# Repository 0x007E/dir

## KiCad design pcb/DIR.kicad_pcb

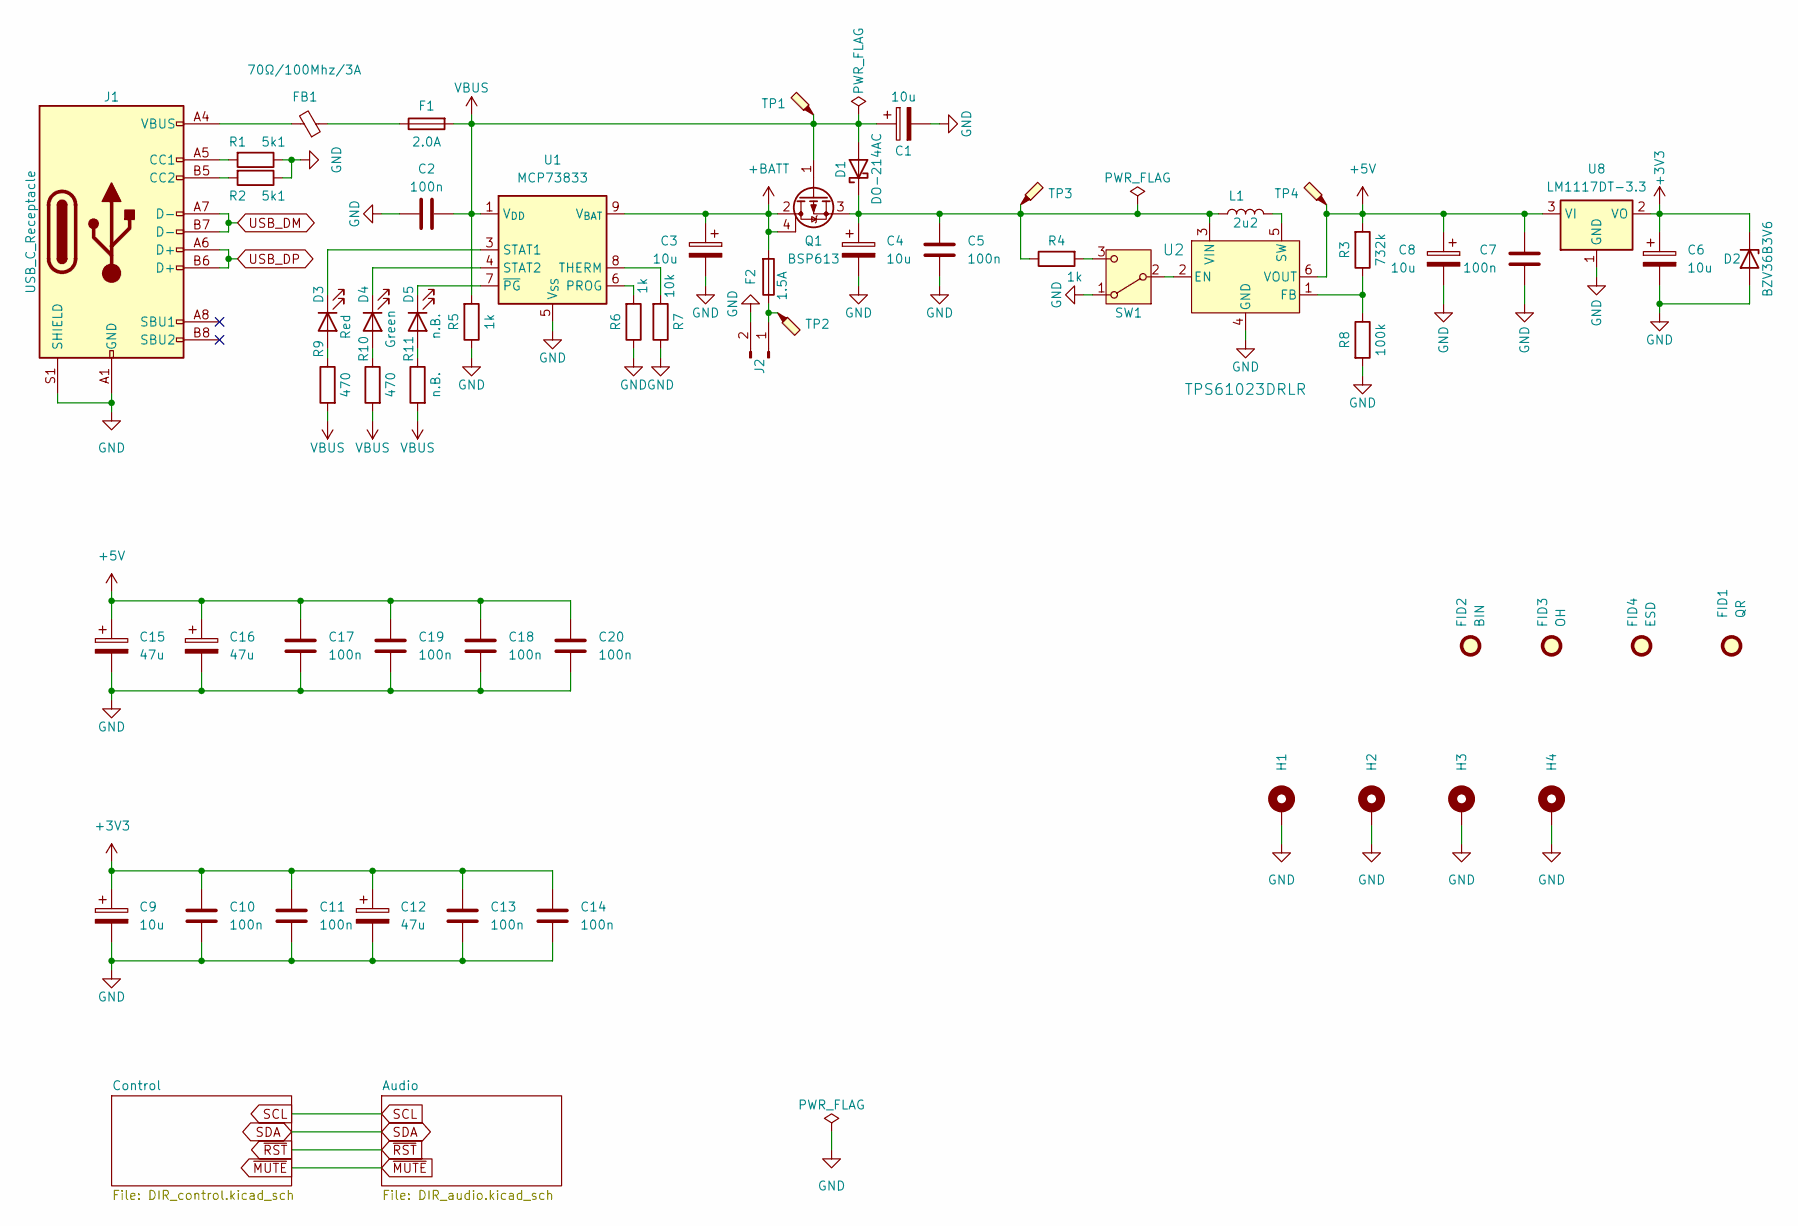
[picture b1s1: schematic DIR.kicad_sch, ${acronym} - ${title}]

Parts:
C1, C3, C4, C6, C8, C9: 10u; CP_EIA-6032-28_Kemet-C
C2, C5, C7, C10, C11, C13, C14, C17, C18, C19, C20: 100n; C_1206_3216Metric
C12, C15, C16: 47u; CP_EIA-6032-28_Kemet-C
D1: DO-214AC; D_SMA
D2: BZV36B3V6; D_MiniMELF
D3: Red; LED_1206_3216Metric
D4: Green; LED_1206_3216Metric
D5: n.B.; LED_1206_3216Metric
F1: 2.0A; Fuse_1206_3216Metric
F2: 1.5A; Fuse_1206_3216Metric
FB1: 70Ω/100Mhz/3A; L_1206_3216Metric
FID1: QR; QR_0x007e_very_small
FID2: BIN; WEEE-Logo_4.2x6mm_SilkScreen
FID3: OH; OSHW-Logo2_7.3x6mm_SilkScreen
FID4: ESD; ESD-Logo_6.6x6mm_SilkScreen
H1, H2: MountingHole_Pad; MountingHole_3.2mm_M3_DIN965_Pad
H3, H4: MountingHole_Pad; MountingHole_2.2mm_M2_Pad
J1: USB_C_Receptacle; USB_C_Receptacle_GCT_USB4110
J2: Conn_01x02_Pin; JST_PH_S2B-PH-K_1x02_P2.00mm_Horizontal
L1: 2u2; L_Vishay_IFSC-1515AH_4x4x1.8mm
Q1: BSP613; SOT-223
R1, R2: 5k1; R_1206_3216Metric
R3: 732k; R_1206_3216Metric
R4, R5, R6: 1k; R_1206_3216Metric
R7: 10k; R_1206_3216Metric
R8: 100k; R_1206_3216Metric
R9, R10: 470; R_1206_3216Metric
R11: n.B.; R_1206_3216Metric
SW1: SW_SPDT; SW_SPDT_CK_JS102011SAQN
TP1, TP2, TP3, TP4: TestPoint_Probe; TestPoint_Pad_D1.0mm
U1: MCP73833; MSOP-10_3x3mm_P0.5mm
U2: TPS61023DRLR; SOT-563
U8: LM1117DT-3.3; TO-252-3_TabPin2

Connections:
+3V3: C6.1, C9.1, C10.1, C11.1, C12.1, C13.1, C14.1, D2.1 (K), U8.2 (VO); also elsewhere on the board
+5V: C7.1, C8.1, C15.1, C16.1, C17.1, C18.1, C19.1, C20.1, R3.2, TP4.1, U2.6 (VOUT), U8.3 (VI); also elsewhere on the board
+BATT: C3.1, F2.2, Q1.2 (D), Q1.4 (D), U1.9 (V_{BAT}), U1.10 (V_{BAT})
GND: C1.2, C2.2, C3.2, C4.2, C5.2, C6.2, C7.2, C8.2, C9.2, C10.2, C11.2, C12.2, C13.2, C14.2, C15.2, C16.2, C17.2, C18.2, C19.2, C20.2, D2.2 (A), H1.1, H2.1, H3.1, H4.1, J1.A1 (GND), J1.A12 (GND), J1.B1 (GND), J1.B12 (GND), J1.S1 (SHIELD), J2.2, R1.1, R2.1, R5.1, R6.1, R7.1, R8.2, SW1.1 (A), U1.5 (V_{SS}), U2.4 (GND), U8.1 (GND); also elsewhere on the board
unnamed: C4.1, C5.1, D1.1 (K), L1.1, Q1.3 (S), R4.1, TP3.1, U2.3 (VIN)
unnamed: D3.2 (A), R9.1
unnamed: D3.1 (K), U1.3 (STAT1)
unnamed: D4.2 (A), R10.1
unnamed: D4.1 (K), U1.4 (STAT2)
unnamed: D5.2 (A), R11.1
unnamed: D5.1 (K), U1.7 (~PG)
unnamed: F1.1, FB1.1
unnamed: FB1.2, J1.A4 (VBUS), J1.A9 (VBUS), J1.B4 (VBUS), J1.B9 (VBUS)
unnamed: J1.A5 (CC1), R1.2
unnamed: J1.B5 (CC2), R2.2
unnamed: F2.1, J2.1, TP2.1
unnamed: SW1.2 (B), U2.2 (EN)
unnamed: R4.2, SW1.3 (C)
unnamed: R6.2, U1.6 (PROG)
unnamed: R7.2, U1.8 (THERM)
unnamed: R3.1, R8.1, U2.1 (FB)
unnamed: L1.2, U2.5 (SW)
USB_DM: J1.A7 (D-), J1.B7 (D-); also elsewhere on the board
USB_DP: J1.A6 (D+), J1.B6 (D+); also elsewhere on the board
VBUS: C1.1, C2.1, D1.2 (A), F1.2, Q1.1 (G), R5.2, R9.2, R10.2, R11.2, TP1.1, U1.1 (V_{DD}), U1.2 (V_{DD}); also elsewhere on the board

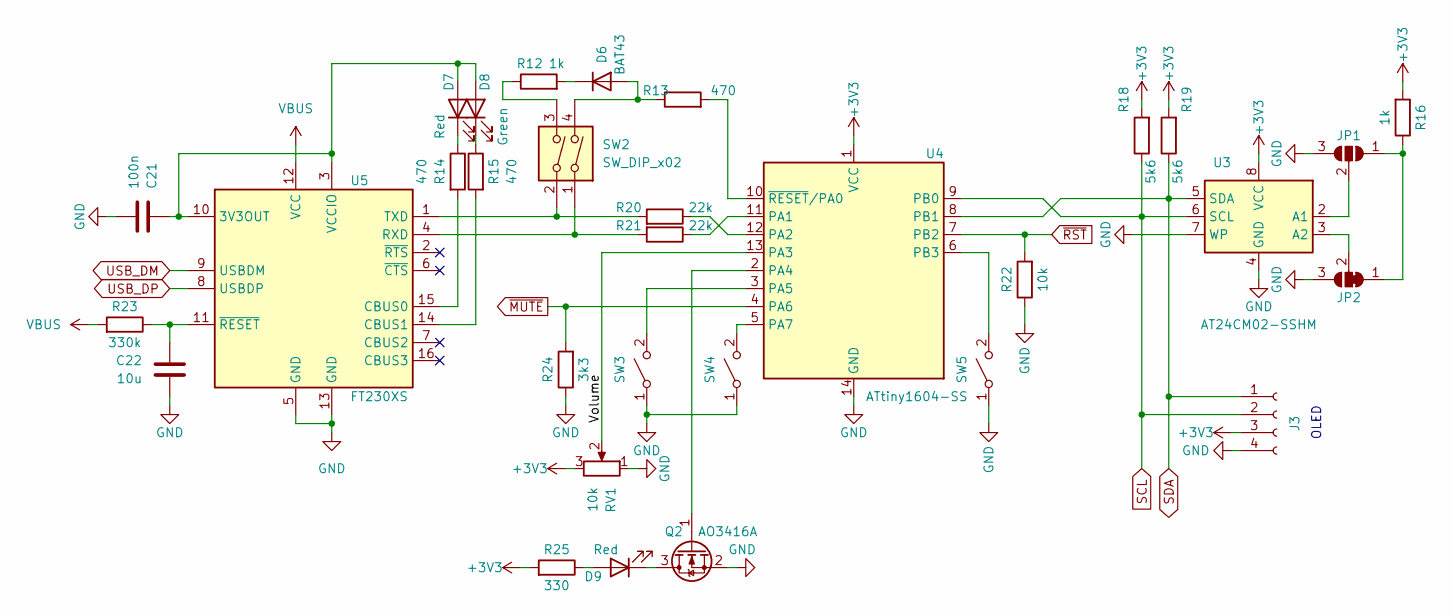
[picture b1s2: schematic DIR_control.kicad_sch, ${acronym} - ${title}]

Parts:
C21: 100n; C_1206_3216Metric
C22: 10u; C_1206_3216Metric
D6: BAT43; D_MiniMELF
D7, D9: Red; LED_1206_3216Metric
D8: Green; LED_1206_3216Metric
J3: Conn_01x04_Socket; PinSocket_1x04_P2.54mm_Vertical
JP1: SolderJumper_3_Open; SolderJumper-3_P1.3mm_Open_RoundedPad1.0x1.5mm_NumberLabels
JP2: SolderJumper_3_Bridged12; SolderJumper-3_P1.3mm_Bridged12_RoundedPad1.0x1.5mm_NumberL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
Q2: AO3416A; SOT-23
R12, R16: 1k; R_1206_3216Metric
R13, R14, R15: 470; R_1206_3216Metric
R18, R19: 5k6; R_1206_3216Metric
R20, R21: 22k; R_1206_3216Metric
R22: 10k; R_1206_3216Metric
R23: 330k; R_1206_3216Metric
R24: 3k3; R_1206_3216Metric
R25: 330; R_1206_3216Metric
RV1: 10k; Potentiometer_Piher_PT-10-V10_Vertical
SW2: SW_DIP_x02; SW_DIP_SPSTx02_Slide_6.7x6.64mm_W8.61mm_P2.54mm_LowProfile
SW3, SW4, SW5: SW_SPST; SW_Tactile_SPST_Angled_PTS645Vx58-2LFS
U3: AT24CM02-SSHM; SOIC-8_3.9x4.9mm_P1.27mm
U4: ATtiny1604-SS; SOIC-14_3.9x8.7mm_P1.27mm
U5: FT230XS; SSOP-16_3.9x4.9mm_P0.635mm

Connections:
+3V3: J3.3, R16.2, R18.2, R19.2, R25.2, RV1.3, U3.8 (VCC), U4.1 (VCC); also elsewhere on the board
/Control/Volume: RV1.2, U4.13 (PA3)
GND: C21.1, C22.2, J3.4, JP1.3 (B), JP2.3 (B), Q2.2 (S), R22.1, R24.1, RV1.1, SW3.1 (A), SW4.1 (A), SW5.1 (A), U3.4 (GND), U3.7 (WP), U4.14 (GND), U5.5 (GND), U5.13 (GND); also elsewhere on the board
unnamed: D6.2 (A), R13.1, SW2.4
unnamed: D6.1 (K), R12.2
unnamed: C21.2, D7.2 (A), D8.2 (A), U5.3 (VCCIO), U5.10 (3V3OUT)
unnamed: D7.1 (K), R14.1
unnamed: D8.1 (K), R15.1
unnamed: D9.2 (A), R25.1
unnamed: D9.1 (K), Q2.3 (D)
unnamed: JP1.1 (A), JP2.1 (A), R16.1
unnamed: JP1.2 (C), U3.2 (A1)
unnamed: JP2.2 (C), U3.3 (A2)
unnamed: Q2.1 (G), U4.2 (PA4)
unnamed: R12.1, SW2.3
unnamed: SW3.2 (B), U4.3 (PA5)
unnamed: SW4.2 (B), U4.5 (PA7)
unnamed: SW5.2 (B), U4.6 (PB3)
unnamed: R21.1, U4.11 (PA1)
unnamed: R20.1, U4.12 (PA2)
unnamed: R13.2, U4.10 (~RESET/PA0)
unnamed: R14.2, U5.15 (CBUS0)
unnamed: R15.2, U5.14 (CBUS1)
unnamed: R21.2, SW2.1, U5.4 (RXD)
unnamed: R20.2, SW2.2, U5.1 (TXD)
unnamed: C22.1, R23.1, U5.11 (~RESET)
SCL: J3.2, R18.1, U3.6 (SCL), U4.9 (PB0); also elsewhere on the board
SDA: J3.1, R19.1, U3.5 (SDA), U4.8 (PB1); also elsewhere on the board
USB_DM: U5.9 (USBDM); also elsewhere on the board
USB_DP: U5.8 (USBDP); also elsewhere on the board
VBUS: R23.2, U5.12 (VCC); also elsewhere on the board
~MUTE: R24.2, U4.4 (PA6); also elsewhere on the board
~RST: R22.2, U4.7 (PB2); also elsewhere on the board

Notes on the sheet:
OLED

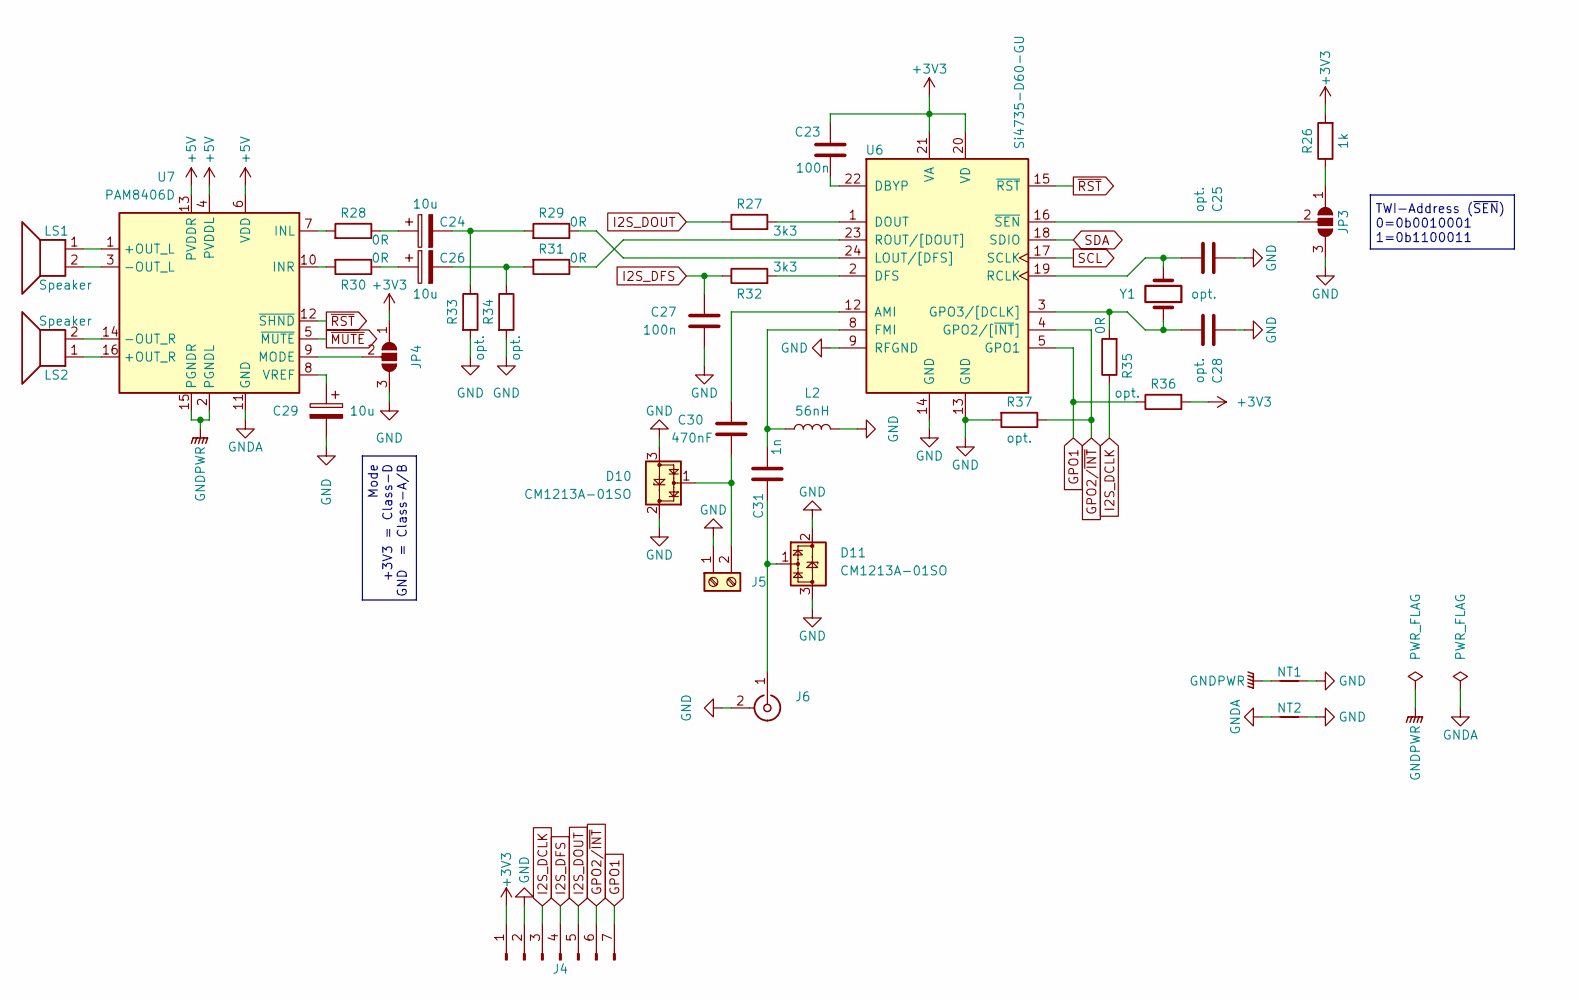
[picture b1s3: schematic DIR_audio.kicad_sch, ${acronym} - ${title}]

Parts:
C23, C27: 100n; C_1206_3216Metric
C24, C26, C29: 10u; CP_Elec_5x5.3
C25, C28: opt.; C_0603_1608Metric
C30: 470nF; C_0603_1608Metric
C31: 1n; C_0603_1608Metric
D10, D11: CM1213A-01SO; SOT-23
J4: Conn_01x07_Pin; PinSocket_1x07_P2.54mm_Horizontal
J5: Screw_Terminal_01x02; WAGO_2060-402_998-404
J6: Conn_Coaxial; SMA_Amphenol_901-143_Horizontal
JP3, JP4: SolderJumper_3_Open; SolderJumper-3_P1.3mm_Open_RoundedPad1.0x1.5mm_NumberLabels
L2: 56nH; L_0603_1608Metric
LS1, LS2: Speaker; WAGO_2060-402_998-404
NT1, NT2: NetTie_2; NetTie-2_SMD_Pad0.5mm
R26: 1k; R_1206_3216Metric
R27, R32: 3k3; R_1206_3216Metric
R28, R29, R30, R31, R35: 0R; R_1206_3216Metric
R33, R34, R36, R37: opt.; R_1206_3216Metric
U6: Si4735-D60-GU; SSOP-24_3.9x8.7mm_P0.635mm
U7: PAM8406D; SOIC-16_3.9x9.9mm_P1.27mm
Y1: opt.; Crystal_SMD_3215-2Pin_3.2x1.5mm

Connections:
+3V3: C23.1, J4.1, JP4.1 (A), R26.2, R36.2, U6.20 (VD), U6.21 (VA); also elsewhere on the board
+5V: U7.4 (PVDDL), U7.6 (VDD), U7.13 (PVDDR); also elsewhere on the board
GND: C25.1, C27.2, C28.1, C29.2, D10.2 (VP), D10.3 (VN), D11.2 (VP), D11.3 (VN), J4.2, J5.1, J6.2 (Ext), JP3.3 (B), JP4.3 (B), L2.2, NT1.2, NT2.2, R33.2, R34.2, R37.2, U6.9 (RFGND), U6.13 (GND), U6.14 (GND); also elsewhere on the board
GNDA: NT2.1, U7.11 (GND)
GNDPWR: NT1.1, U7.2 (PGNDL), U7.15 (PGNDR)
GPO1: J4.7, R36.1, U6.5 (GPO1)
GPO2/~INT: J4.6, R37.1, U6.4 (GPO2/[~INT])
I2S_DCLK: J4.3, R35.1
I2S_DFS: C27.1, J4.4, R32.1
I2S_DOUT: J4.5, R27.1
unnamed: C24.1, R28.1
unnamed: C24.2, R29.2, R33.1
unnamed: C26.1, R30.1
unnamed: C26.2, R31.2, R34.1
unnamed: C30.2, D10.1 (CH1), J5.2
unnamed: C31.1, D11.1 (CH1), J6.1 (In)
unnamed: JP3.1 (A), R26.1
unnamed: JP3.2 (C), U6.16 (~SEN)
unnamed: JP4.2 (C), U7.9 (MODE)
unnamed: C30.1, U6.12 (AMI)
unnamed: C23.2, U6.22 (DBYP)
unnamed: R32.2, U6.2 (DFS)
unnamed: R27.2, U6.1 (DOUT)
unnamed: C31.2, L2.1, U6.8 (FMI)
unnamed: C28.2, R35.2, U6.3 (GPO3/[DCLK]), Y1.1
unnamed: R29.1, U6.24 (LOUT/[DFS])
unnamed: C25.2, U6.19 (RCLK), Y1.2
unnamed: R31.1, U6.23 (ROUT/[DOUT])
unnamed: LS1.1, U7.1 (+OUT_L)
unnamed: LS2.1, U7.16 (+OUT_R)
unnamed: LS1.2, U7.3 (-OUT_L)
unnamed: LS2.2, U7.14 (-OUT_R)
unnamed: R28.2, U7.7 (INL)
unnamed: R30.2, U7.10 (INR)
unnamed: C29.1, U7.8 (VREF)
SCL: U6.17 (SCLK); also elsewhere on the board
SDA: U6.18 (SDIO); also elsewhere on the board
~MUTE: U7.5 (~MUTE); also elsewhere on the board
~RST: U6.15 (~RST), U7.12 (~SHND); also elsewhere on the board

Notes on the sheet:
Mode +3V3 = Class-D GND = Class-A/B
TWI-Address (~{SEN}) 0=0b0010001 1=0b1100011

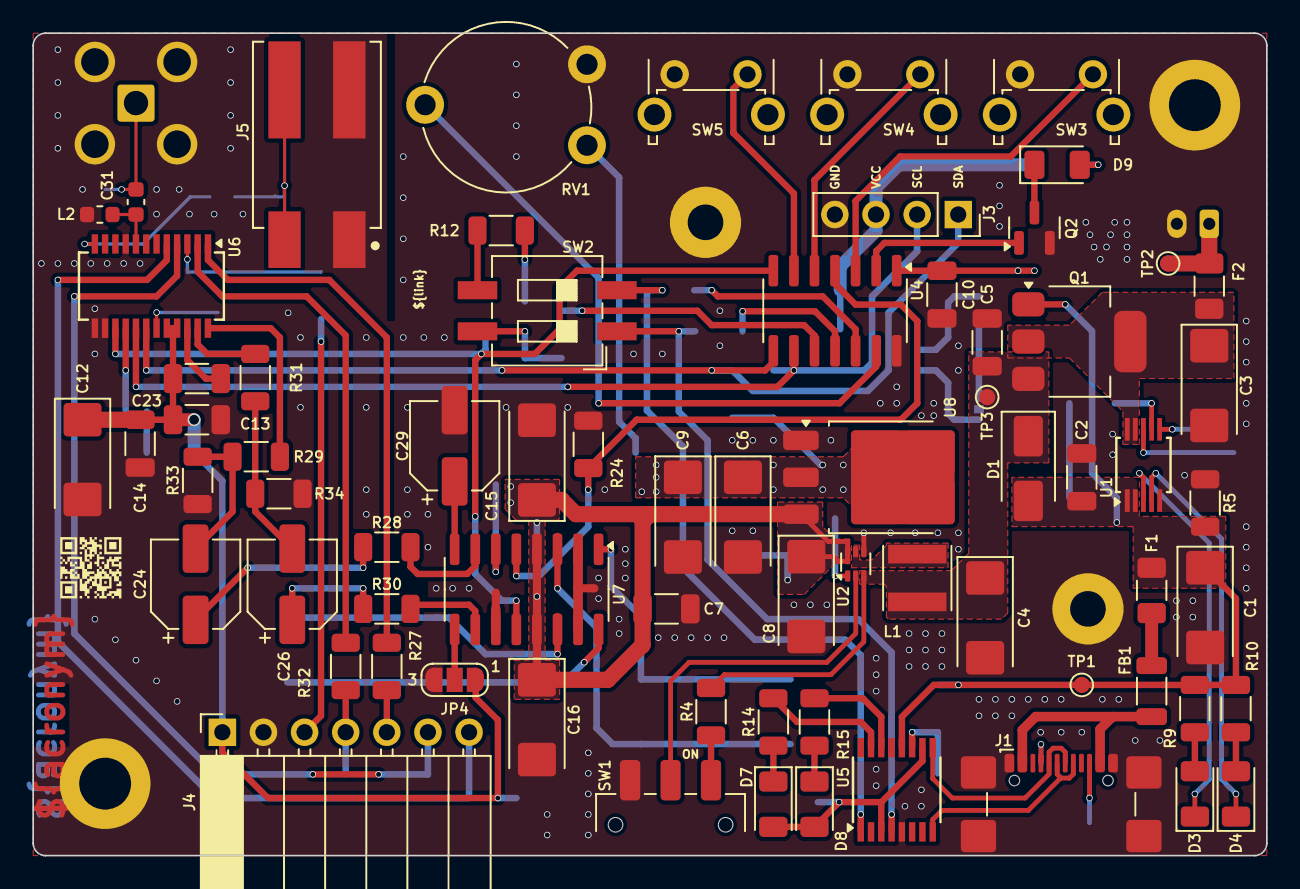
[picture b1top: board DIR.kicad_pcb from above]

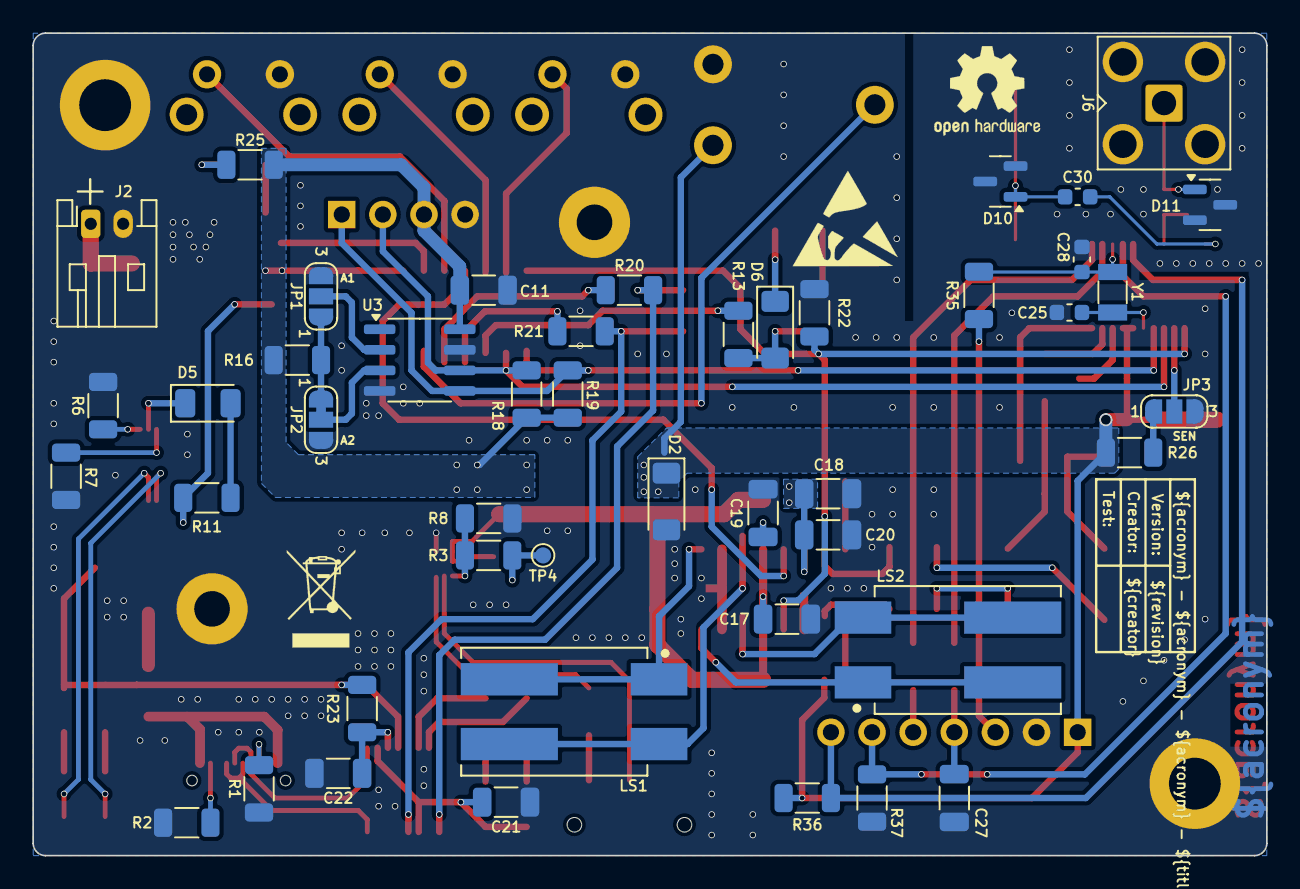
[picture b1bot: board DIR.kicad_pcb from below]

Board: 2 copper layers, 76.2 x 50.8 mm, 126 parts (49 on the bottom side), 85 nets.

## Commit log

2026-02-18 Add pcb layout
2026-03-04 Rename LICENSE
2026-03-04 Add build pipeline
2026-03-18 Add missing vendor
2026-03-18 Fix silkscreen position
2026-03-18 Remove optional vendors
2026-03-25 Fix wrong vendor-id
2026-03-25 Repositioning of overlapping reference and value
2026-03-26 Fix TWI address description
2026-03-27 Change Z-Diode to 3V3
2026-03-27 Fix power path issue
2026-03-27 Change SHDN and MUTE pins
2026-03-27 Modify pcb position
2026-03-28 Fix 3d oled rotation
2026-03-28 Add dimensioning
2026-03-29 Add mechanical parts
2026-03-30 Add buttons and switch
2026-03-30 Change env variables to upper case
2026-03-30 Add FreeCAD job
2026-04-15 Optimize push-button position

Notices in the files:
parts and their libraries:
license: CC BY-NC-SA 4.0
